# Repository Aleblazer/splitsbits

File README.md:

# splitsbits
Split stickless fight pad

To-Do:
Add mounting holes for 3D printed cases

Left side WASD version

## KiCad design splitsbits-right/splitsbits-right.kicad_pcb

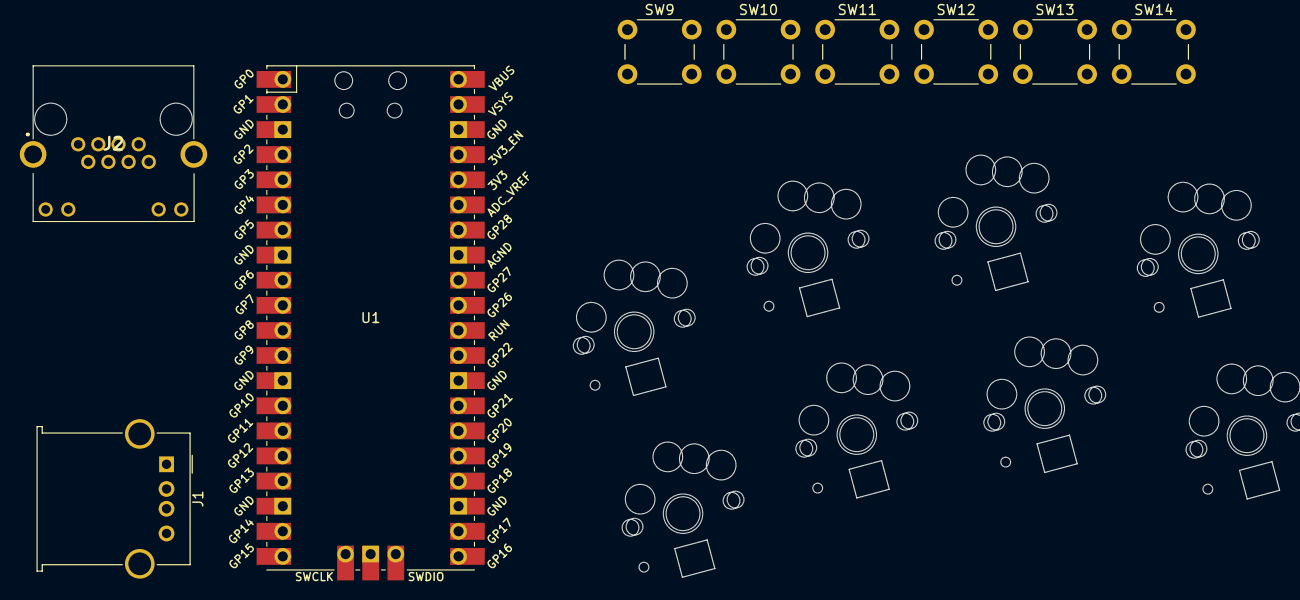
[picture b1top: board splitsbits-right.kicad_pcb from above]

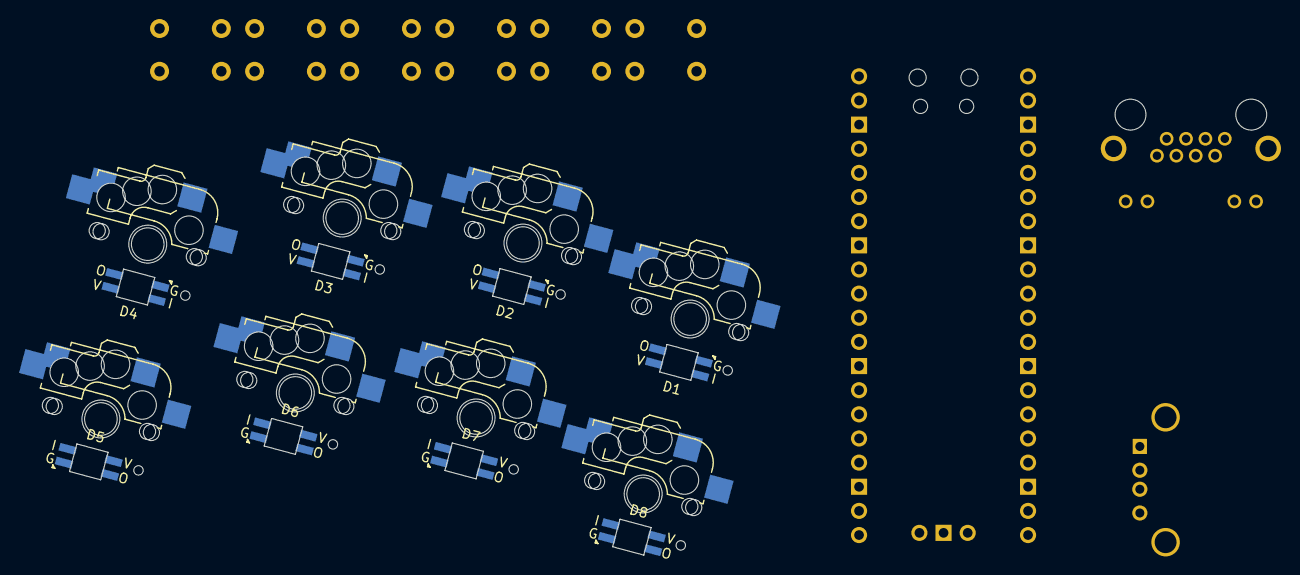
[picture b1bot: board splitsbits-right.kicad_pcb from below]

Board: 2 copper layers, 25 parts (8 on the bottom side), 31 nets, no tracks yet.

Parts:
D1, D2, D3, D4, D5, D6, D7, D8: SK6812MINI-E_Easy_Solder; YS-SK6812MINI-E-SingleSide
J1: USB_A; USB_A_Molex_67643_Horizontal
J2: RJ45; RRJ45R08PC000
SW1, SW2, SW3, SW4, SW5, SW6, SW7, SW8: SW_Push_45deg; Kailh_socket_MX-ChocV1
SW9, SW10, SW11, SW12, SW13, SW14: SW_Push_45deg; SW_PUSH_6mm
U1: Pico; RPi_Pico_SMD_TH

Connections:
A1: SW13.1, U1.26 (GPIO20)
A2: SW14.1, U1.27 (GPIO21)
B1: SW1.1, U1.9 (GPIO6)
B2: SW2.1, U1.10 (GPIO7)
B3: SW5.1, U1.14 (GPIO10)
B4: SW6.1, U1.15 (GPIO11)
Down: J2.3, U1.5 (GPIO3)
GND: D1.3 (VSS), D2.3 (VSS), D3.3 (VSS), D4.3 (VSS), D5.3 (VSS), D6.3 (VSS), D7.3 (VSS), D8.3 (VSS), J1.4 (GND), J2.8, SW1.2, SW2.2, SW3.2, SW4.2, SW5.2, SW6.2, SW7.2, SW8.2, SW9.2, SW10.2, SW11.2, SW12.2, SW13.2, SW14.2, U1.3 (GND), U1.8 (GND), U1.13 (GND), U1.18 (GND), U1.23 (GND), U1.28 (GND), U1.38 (GND)
HostUSB-D+: J1.3 (D+), U1.31 (GPIO26_ADC0)
HostUSB-D-: J1.2 (D-), U1.32 (GPIO27_ADC1)
L1: SW8.1, U1.17 (GPIO13)
L2: SW4.1, U1.12 (GPIO9)
L3: SW11.1, U1.24 (GPIO18)
LED: D1.4 (DIN), U1.34 (GPIO28_ADC2)
LED-OUT: D8.2 (DOUT), J2.6
Left: J2.5, U1.7 (GPIO5)
unnamed: D1.2 (DOUT), D2.4 (DIN)
unnamed: D2.2 (DOUT), D3.4 (DIN)
unnamed: D3.2 (DOUT), D4.4 (DIN)
unnamed: D4.2 (DOUT), D5.4 (DIN)
unnamed: D5.2 (DOUT), D6.4 (DIN)
unnamed: D6.2 (DOUT), D7.4 (DIN)
unnamed: D7.2 (DOUT), D8.4 (DIN)
R1: SW7.1, U1.16 (GPIO12)
R2: SW3.1, U1.11 (GPIO8)
R3: SW12.1, U1.25 (GPIO19)
Right: J2.4, U1.6 (GPIO4)
S1: SW9.1, U1.21 (GPIO16)
S2: SW10.1, U1.22 (GPIO17)
Up: J2.2, U1.4 (GPIO2)
VCC: D1.1 (VDD), D2.1 (VDD), D3.1 (VDD), D4.1 (VDD), D5.1 (VDD), D6.1 (VDD), D7.1 (VDD), D8.1 (VDD), J1.1 (VBUS), J2.1, U1.40 (VBUS)

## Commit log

2023-08-19 Right side layout started
2024-04-09 Left Flatbox-Style Done
    Pending Left WASD-Style
